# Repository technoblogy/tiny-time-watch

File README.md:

# Tiny Time Watch
ATtiny85-based watch showing the time on 12 LEDs.
For more information see: http://www.technoblogy.com/show?1JH5.

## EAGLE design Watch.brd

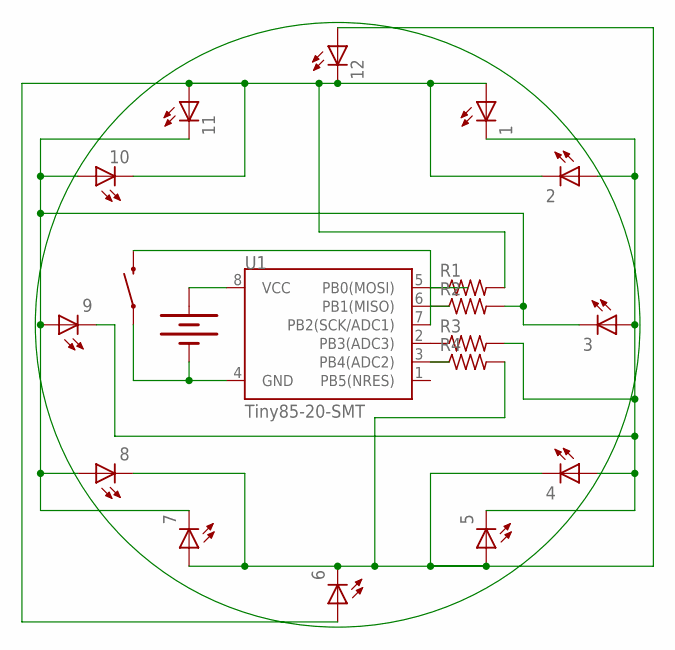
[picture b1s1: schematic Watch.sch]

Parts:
1, 2, 3, 4, 5, 6, 7, 8, 9, 10, 11, 12: LEDCHIPLED_0805; CHIPLED_0805
BAT1: 20mm coincell; BATTCON_20MM_4LEGS
R1, R2, R3, R4: R-US_M0805; M0805
S2: SWITCH-MOMENTARY-2SMD; TACTILE-SWITCH-SMD
U1: Tiny85-20-SMT; SO08-EIAJ

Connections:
unnamed: 1.C, 2.A, 3.A, 4.A, 5.C, 9.C, R3.2
unnamed: 4.C, 5.A, 6.C, 7.A, 8.C, 12.A, R4.2
unnamed: 3.C, 7.C, 8.A, 9.A, 10.A, 11.C, R2.2
unnamed: 1.A, 2.C, 6.A, 10.C, 11.A, 12.C, R1.2
unnamed: R1.1, U1.5 (PB0(MOSI))
unnamed: R2.1, U1.6 (PB1(MISO))
unnamed: R3.1, U1.2 (PB3(ADC3))
unnamed: R4.1, U1.3 (PB4(ADC2))
unnamed: BAT1.NEGATIVE (-), S2.1, U1.4 (GND)
unnamed: S2.3 (2), U1.7 (PB2(SCK/ADC1))
unnamed: BAT1.POSITIVE@1 (+), BAT1.POSITIVE@2 (+), BAT1.POSITIVE@3 (+), BAT1.POSITIVE@4 (+), U1.8 (VCC)

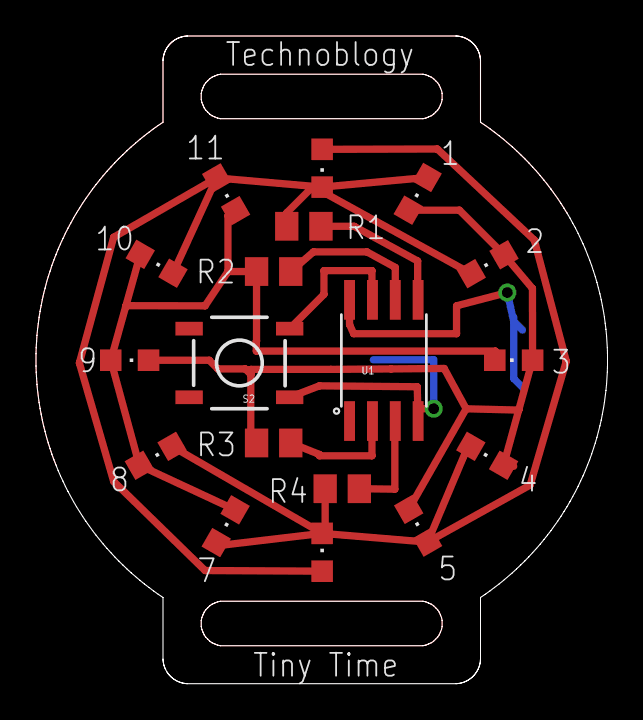
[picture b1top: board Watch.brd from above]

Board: 2 copper layers, 31.7 x 36.0 mm, 19 parts (1 on the bottom side), 11 nets.

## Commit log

2016-12-03 Version 1 - 3rd December 2016
2016-12-03 Version 1 - Eagle files
2016-12-05 Added link to article.

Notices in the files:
parts and their libraries:
SparkFun-DigitalIC: Licensing: Creative Commons ShareAlike 4.0 International - https://creativecommons.org/licenses/by-sa/4.0
